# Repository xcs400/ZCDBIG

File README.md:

**Detecteur de passage à 0V**<br><br>
Montage avec composants trad. et pcb "simple face" maximalisé pour realisation home-made à la fraiseuse ou par gravure chimique<br>
Le projet Kicad complet est fourni<br>

relevé:

Ce montage a été integré dans mon router solaire pour commander la seconde voie utilisant le SSR.<br>
La premiere voie utilise le SSL commandé en PWM (la detection de passage a 0 est integré dans le SSL).

Le logiciel de gestion est une version modifié de YARSOL . <br>
La modification consiste principalement en un module de communication directe vers Tuya ("wifi bidirectional meter") placé dans mon tableau electrique pour acceder à la consomation de la maison.
  <br>
Le rafraississement des informations de puissance se fait toutes les 3 secondes par wifi  (limite du module tuya), et ne necesssite pas l'utilisation de home assistant ou de serveur MQTT.

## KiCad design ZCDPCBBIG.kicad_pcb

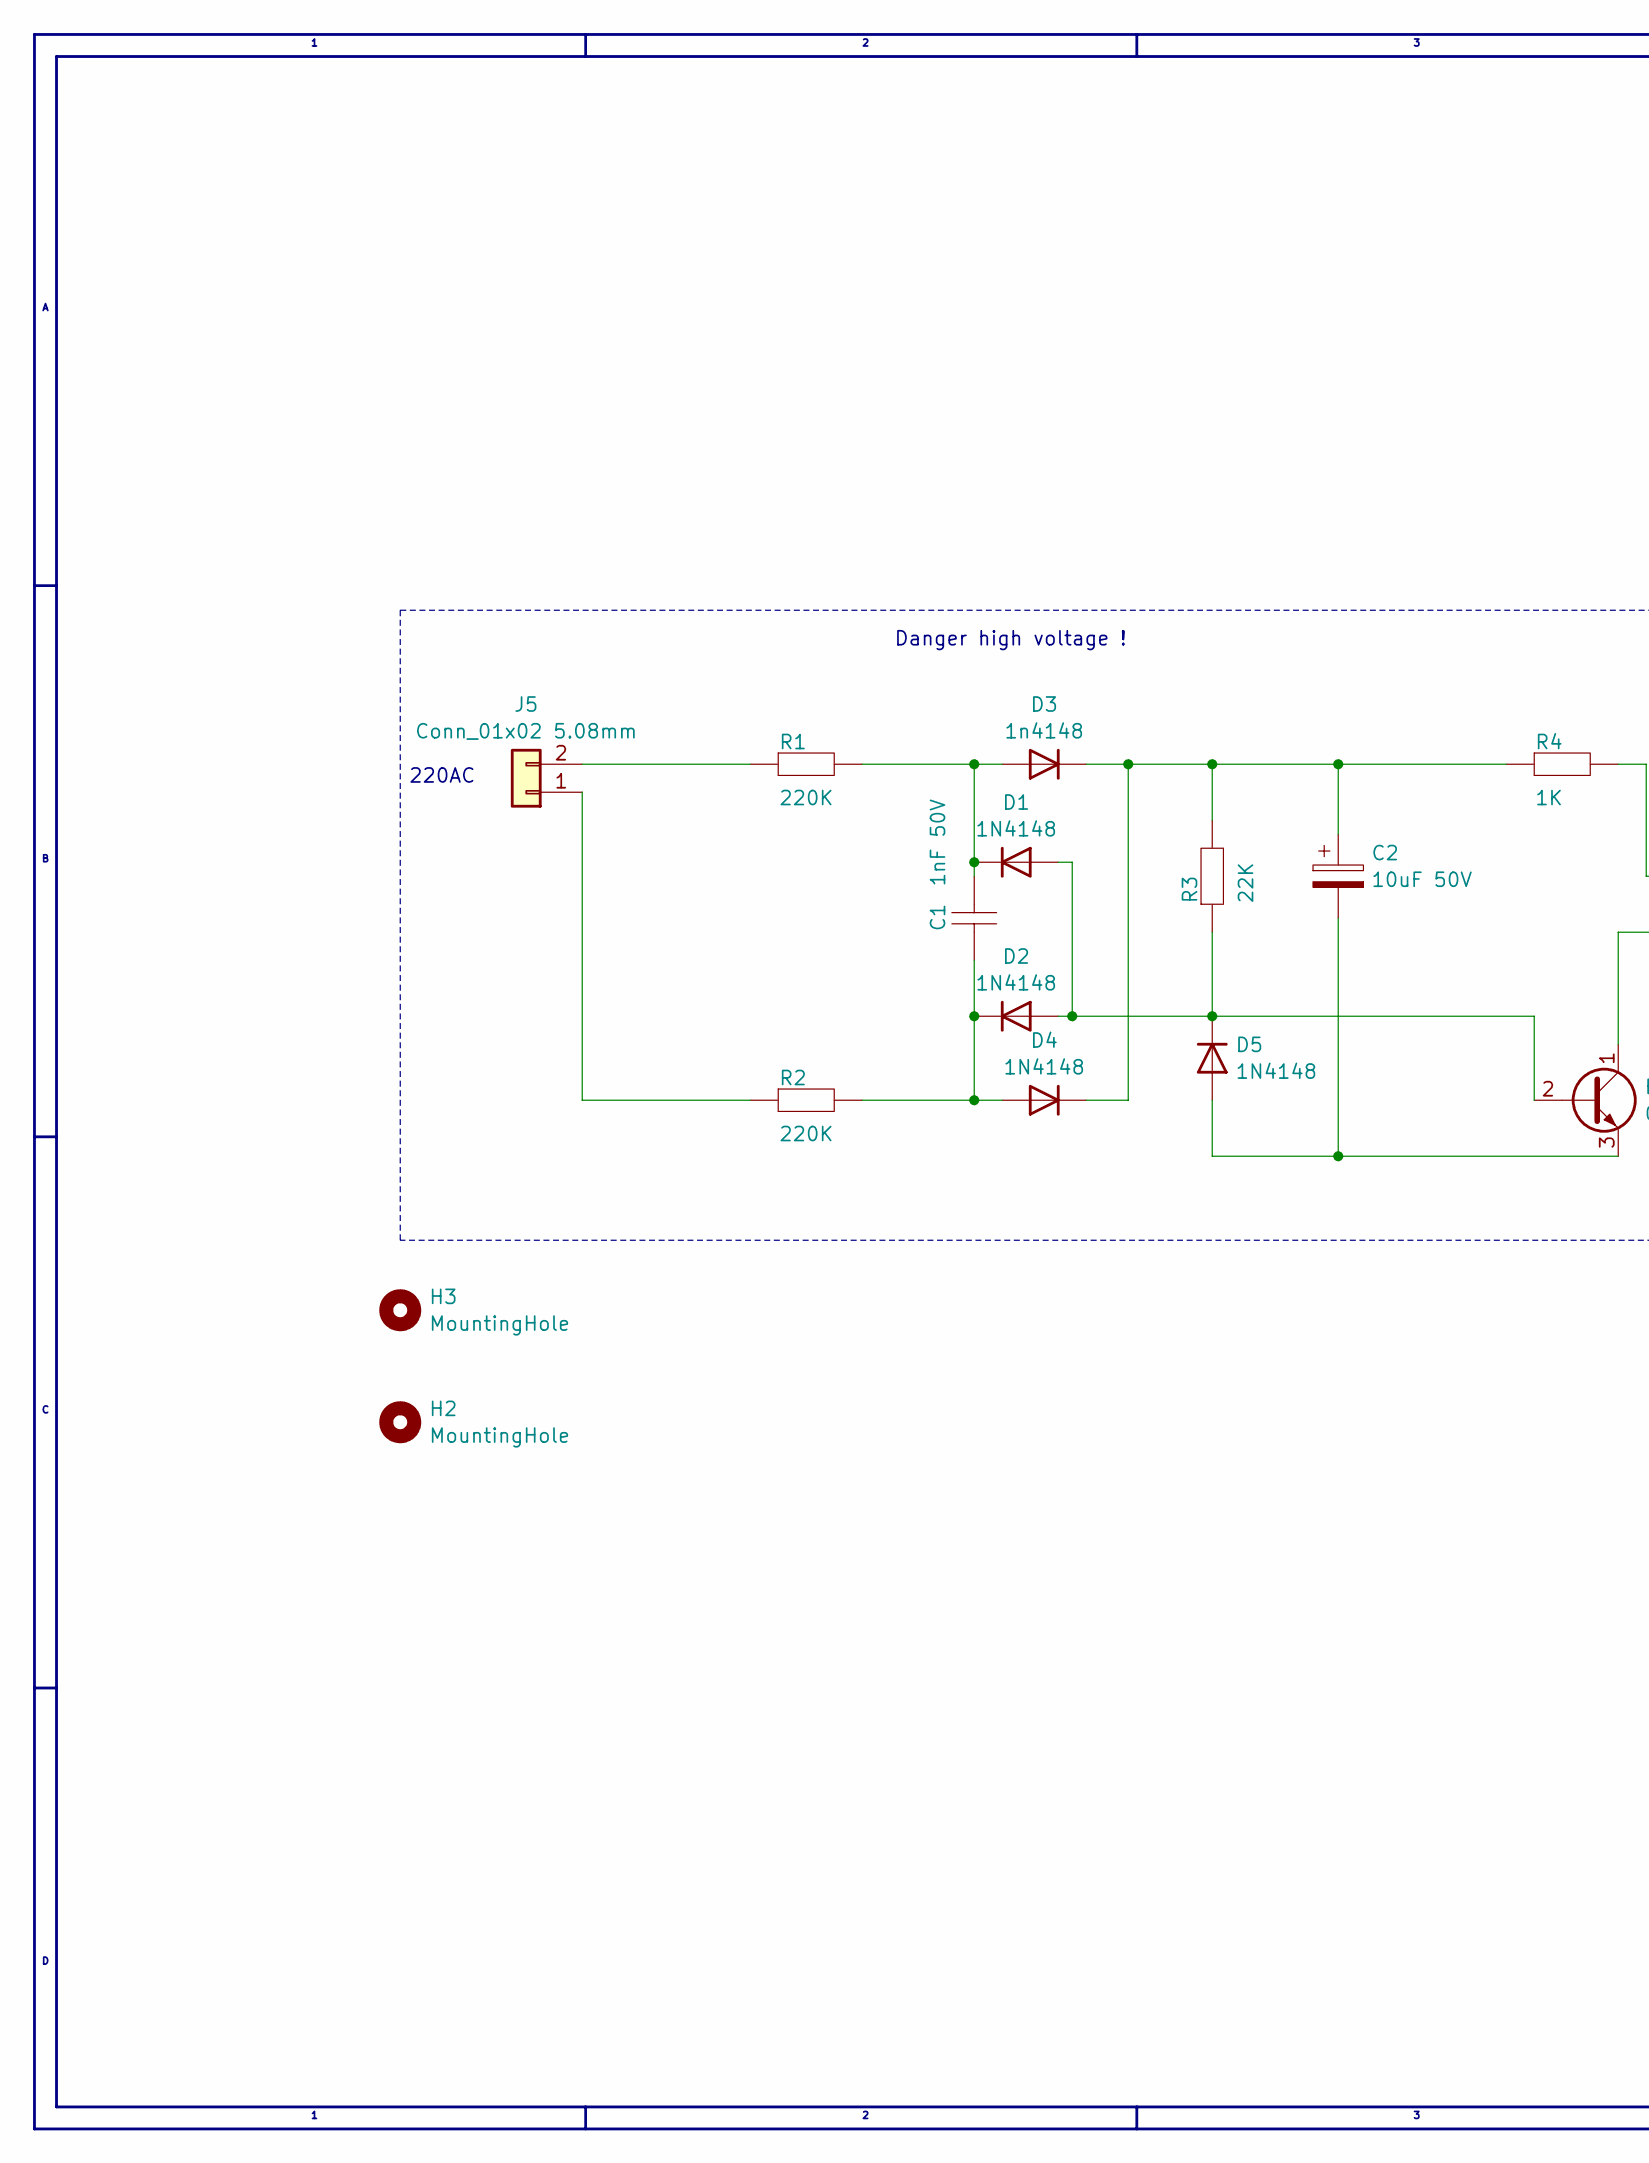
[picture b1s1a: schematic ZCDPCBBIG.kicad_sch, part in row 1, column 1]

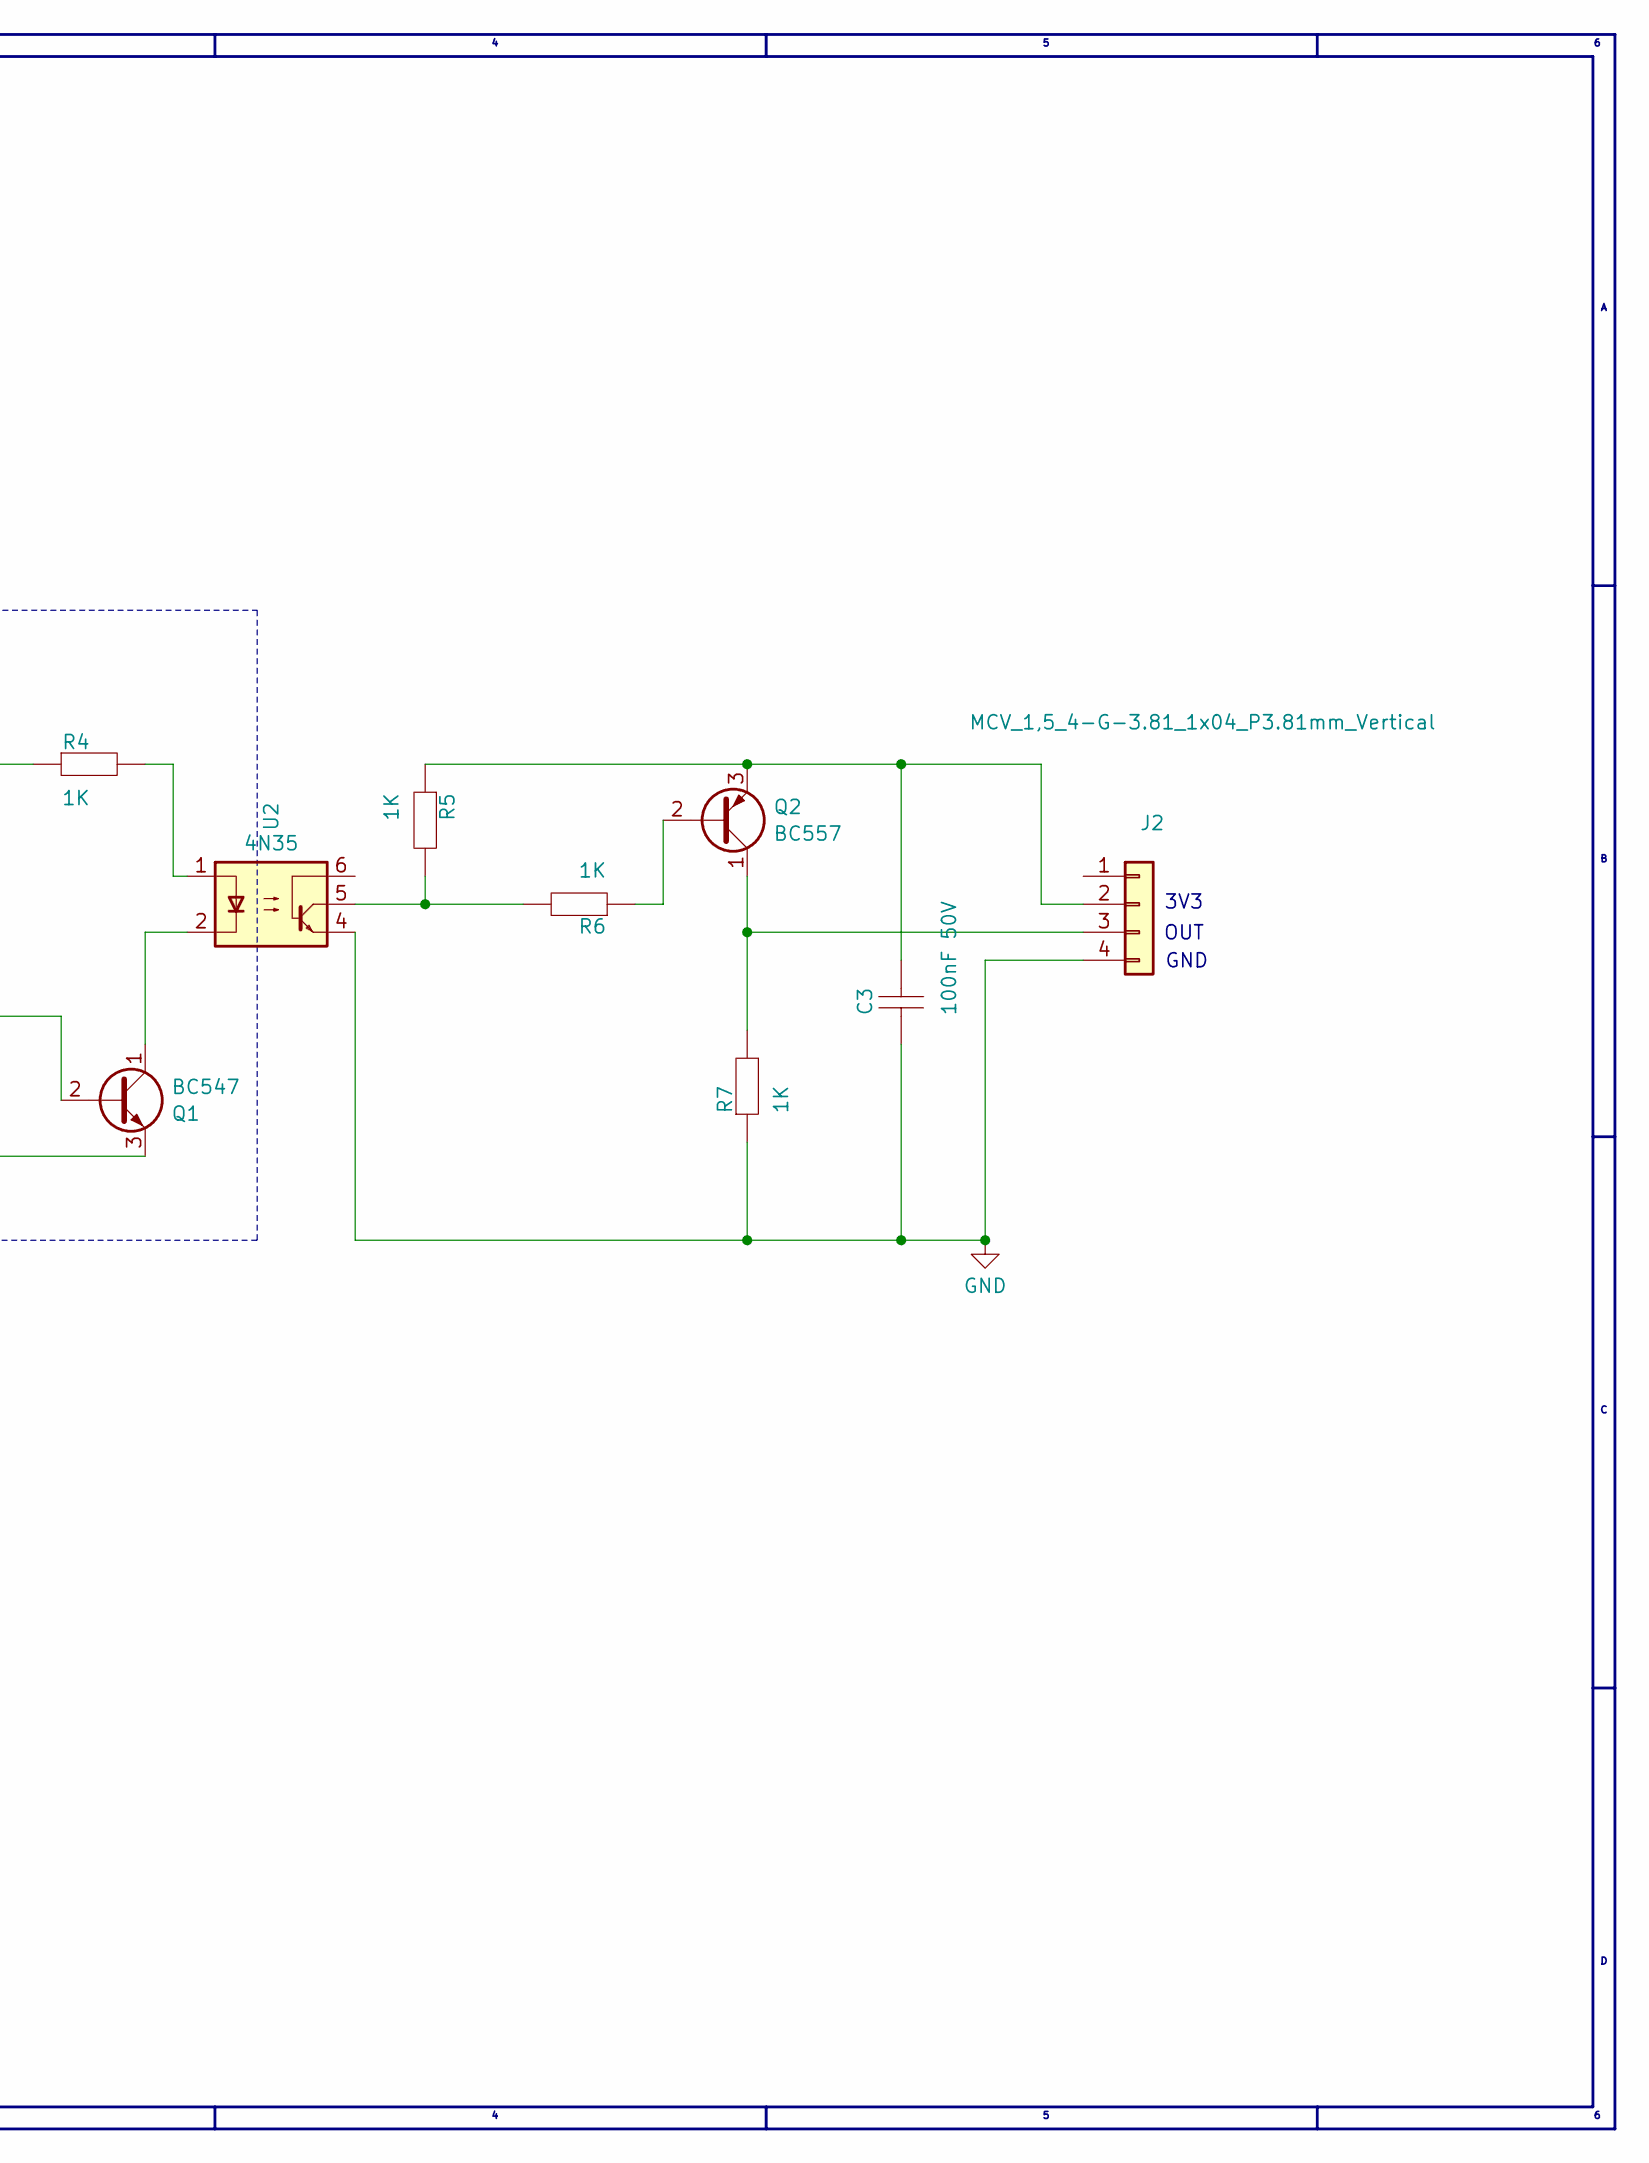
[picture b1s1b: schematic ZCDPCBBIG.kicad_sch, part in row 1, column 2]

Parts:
C1: 1nF 50V; C_Disc_D6.0mm_W2.5mm_P5.00mm_big
C2: 10uF 50V; CAPPRD200W55D500H1350_big
C3: 100nF 50V; C_Disc_D6.0mm_W2.5mm_P5.00mm_big
D1, D2, D4, D5: 1N4148; D_DO-35_SOD27_P7.62mm_Horizontal_big
D3: 1n4148; D_DO-35_SOD27_P7.62mm_Horizontal_big
H2, H3: MountingHole; MountingHole_3.2mm_M3
J2: MCV_1,5_4-G-3.81_1x04_P3.81mm_Vertical; PhoenixContact_MCV_1,5_4-G-3.81_1x04_P3.81mm_Vertical_route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
J5: Conn_01x02 5.08mm; PhoenixContact_MCV_1,5_2-G-5.08_1x02_P5.08mm_Vertical_route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
Q1: BC547; TO-92_Inline_router_big
Q2: BC557; TO-92_Inline_router_big
R1, R2: 220K; R_Axial_DIN0207_L6.3mm_D2.5mm_P10.16mm_Horizontal_big
R3: 22K; R_Axial_DIN0207_L6.3mm_D2.5mm_P10.16mm_Horizontal_big
R4, R5, R6, R7: 1K; R_Axial_DIN0207_L6.3mm_D2.5mm_P10.16mm_Horizontal_big
U2: 4N35; DIP-6_W7.62mm_big

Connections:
GND: C3.1, J2.4, R7.1, U2.4
unnamed: D1.2 (A), D2.2 (A), D5.1 (K), Q1.2 (B), R3.1
unnamed: C1.2, D1.1 (K), D3.2 (A), R1.2
unnamed: C1.1, D2.1 (K), D4.2 (A), R2.2
unnamed: C2.1, D3.1 (K), D4.1 (K), R3.2, R4.1
unnamed: C2.2, D5.2 (A), Q1.3 (E)
unnamed: C3.2, J2.2, Q2.3 (E), R5.1
unnamed: J2.3, Q2.1 (C), R7.2
unnamed: J5.1, R2.1
unnamed: J5.2, R1.1
unnamed: Q1.1 (C), U2.2
unnamed: Q2.2 (B), R6.1
unnamed: R4.2, U2.1
unnamed: R5.2, R6.2, U2.5

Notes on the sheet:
OUT
220AC
Danger high voltage !
3V3
GND

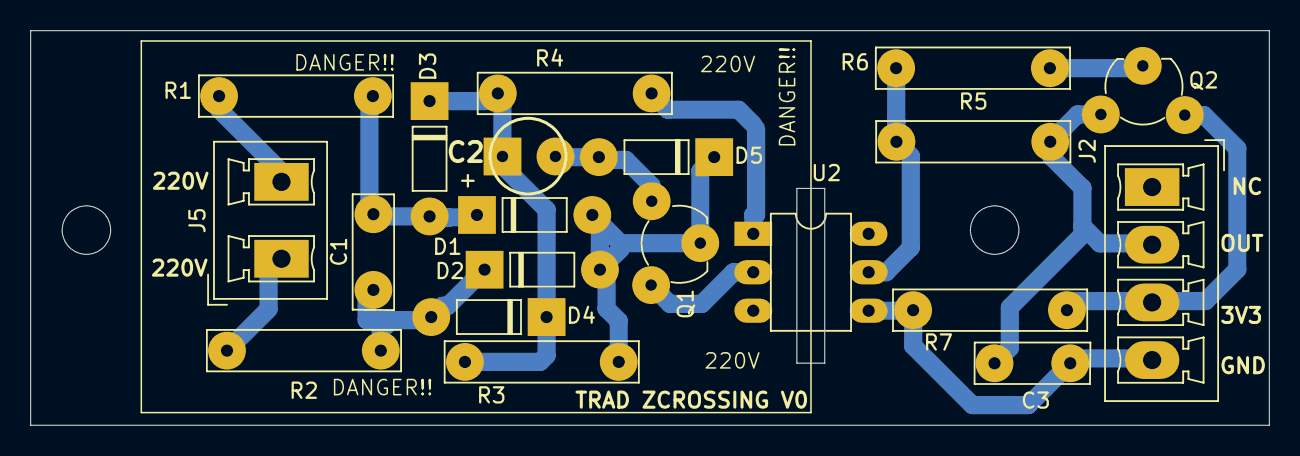
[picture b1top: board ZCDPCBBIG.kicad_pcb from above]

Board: 2 copper layers, 81.8 x 26.1 mm, 22 parts (0 on the bottom side), 14 nets.

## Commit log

2025-11-15 init
2025-11-15 Add project description and images to README
2025-11-16 add routage
2025-11-16 Revise README formatting and update image links
    Updated images and formatting in README.
2025-11-16 Enhance README with detailed project description
    Updated project description with additional details for home-made implementation.
2025-11-16 ajout releve scope
2025-11-17 ajout routeur
2025-11-17 readme
